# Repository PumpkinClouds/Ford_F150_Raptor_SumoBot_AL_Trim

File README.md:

# Ford_F150_Raptor_SumoBot_AL_Trim
Sumo Bot Designed by Minh Nguyen, David Hong, Nathan Wignall, and Ana Wise

This Repository contains the code and pcb design for the sumo bot.

The "Ford F150" is a unique 4 wheeled sumo bot

PCB Design Software: KiCad

Microcontroller used: STM32F303CCT6 ([datasheet]([url](https://www.st.com/content/ccc/resource/technical/document/datasheet/f2/1f/e1/41/ef/59/4d/50/DM00058181.pdf/files/DM00058181.pdf/jcr:content/translations/en.DM00058181.pdf)))

Microcontroller Programming Framework: 

3 IR Distance Sensors: Adafruit GP2Y0A21YK0F [Link]([url](https://www.adafruit.com/product/164)) 

4 JSumo ML1 Line Sensors: JSumo JS16249 [Link]([url](https://www.jsumo.com/micro-line-sensor-ml1))

Bot code and pcb for sumo bot competition. (Asgore's fault)

## Contributing to the Project

### Software Dependencies
- [ ] KiCAD
- [ ] A text editor
- [ ] (Optional) Nix + Flakes + Direnv, automatically sets up a development enviornment to work on the project with

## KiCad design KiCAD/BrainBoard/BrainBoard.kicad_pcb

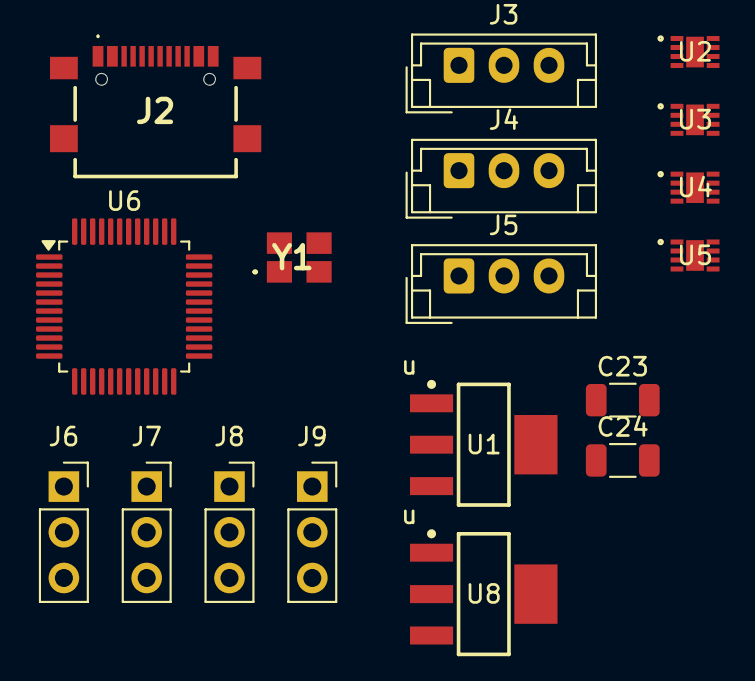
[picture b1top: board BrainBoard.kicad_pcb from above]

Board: 2 copper layers, 18 parts (0 on the bottom side), 25 nets, no tracks yet.

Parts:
C23: 0.47uF; C_1206_3216Metric
C24: 22uF; C_1206_3216Metric
J2: USB4216-03-A; USB421603A
J3, J4, J5: Conn_01x03_Socket; JST_EH_B3B-EH-A_1x03_P2.50mm_Vertical
J6, J7, J8, J9: Conn_01x03_Socket; PinSocket_1x03_P2.54mm_Vertical
U1: TLV1117-33; DCY0004A_N
U2, U3, U4, U5: DRV8231DSGR; WSON8_DRV8231_TEX
U6: STM32F303CCTx; LQFP-48_7x7mm_P0.5mm
U8: LM2940IMPX-5.0/NOPB; DCY0004A_N
Y1: NX3225SA-32.000MHZ-STD-CSR-1; NX3225SA32000MHZSTDCSR1

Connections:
+3.3V: J6.2, J7.2, J8.2, J9.2, U1.2 (VO), U2.4 (VREF), U3.4 (VREF), U4.4 (VREF), U5.4 (VREF), U6.1 (VBAT), U6.24 (VDD), U6.36 (VDD), U6.48 (VDD)
+5V: J3.1, J4.1, J5.1
+BATT: C23.1, U1.3 (VI), U2.5 (VM), U3.5 (VM), U4.5 (VM), U5.5 (VM), U8.1 (IN)
/Distance Sensors/DIST_SENS_1: J3.3, U6.21 (PB10)
/Distance Sensors/DIST_SENS_2: J4.3, U6.25 (PB12)
/Distance Sensors/DIST_SENS_3: J5.3, U6.26 (PB13)
/Line Sensors/LINE_1: J6.1, U6.13 (PA3)
/Line Sensors/LINE_2: J7.1, U6.19 (PB1)
/Line Sensors/LINE_3: J8.1, U6.38 (PA15)
/Line Sensors/LINE_4: J9.1, U6.45 (PB8)
/Motor Drivers/IN1_A: U3.3 (IN1), U6.11 (PA1)
/Motor Drivers/IN1_B: U2.3 (IN1), U6.16 (PA6)
/Motor Drivers/IN1_C: U4.3 (IN1), U6.43 (PB7)
/Motor Drivers/IN1_D: U5.3 (IN1), U6.27 (PB14)
/Motor Drivers/IN2_A: U3.2 (IN2), U6.12 (PA2)
/Motor Drivers/IN2_B: U2.2 (IN2), U6.17 (PA7)
/Motor Drivers/IN2_C: U4.2 (IN2), U6.42 (PB6)
/Motor Drivers/IN2_D: U5.2 (IN2), U6.28 (PB15)
/STM32F303CCT6 Microcontroller/HSE_IN: U6.5 (PF0), Y1.1 (XTAL_1)
/STM32F303CCT6 Microcontroller/HSE_OUT: U6.6 (PF1), Y1.3 (XTAL_2)
/STM32F303CCT6 Microcontroller/USB_D+: J2.A6 (DP1), J2.B6 (DP2), U6.33 (PA12)
/STM32F303CCT6 Microcontroller/USB_D-: J2.A7 (DN1), J2.B7 (DN2), U6.32 (PA11)
/STM32F303CCT6 Microcontroller/USB_VBUS: J2.A4 (VBUS_1), J2.B4 (VBUS_2)
/Voltage Regulator/5V: C24.1, U8.3 (OUT)
GND: C23.2, C24.2, J2.A1 (GND_1), J2.B1 (GND_2), J2.G1 (GND_3), J2.G2 (GND_4), J2.G3 (GND_5), J2.G4 (GND_6), J3.2, J4.2, J5.2, J6.3, J7.3, J8.3, J9.3, U1.1 (GND), U6.8 (VSSA), U6.23 (VSS), U6.35 (VSS), U6.47 (VSS), Y1.2 (GND_1), Y1.4 (GND_2)

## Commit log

2025-09-29 kicad files
2025-09-29 refactor: adding some dev files and reorganizing file structure
2025-09-29 docs: minimal update to README for contributions
2025-09-29 Update flakes with support for markdown and git utils
2025-09-30 add folders for footprints, symbols, and 3d-models
2025-09-30 [feat] add voltage regulator
2025-09-30 [bug] make ERC happy
2025-09-30 [docs] update page settings
2025-09-30 initial PIO project creation
2025-09-30 [fix] replace linear regulator
2025-09-30 [feat] add example motor driver
2025-10-02 [feature] Finalize DRV8231DSGR motor drivers
2025-10-06 feat: Processor add
2025-10-06 fix: Make DRC happy
2025-10-07 refactor(Software): change the PIO framework to `libopencm3`
2025-10-07 chore(Software): update .gitignore to ignore `.cache/` and `.platformio/`
2025-10-07 feat(Software): add additional project files (VSCode and .clang-format)
2025-10-07 feat(KiCad): Add a .gitignore for KiCad project
2025-10-13 feat: add second battery
2025-10-18 Added and finalized GPIO and PWM pinouts
2025-10-18 feat: added hierarchy pins to global sheet
2025-10-20 feat: Connect microcontroller pwm signals into motor drivers
2025-10-20 feat: battery input
2025-10-20 fix: correct nominal voltage
2025-10-24 refactor(Software): change framework from libopencm3 to stm32_hal
2025-10-24 feat(Software): Additional pin setup
2025-10-28 feat: added hiearchal power pins to microcontroller to avoid having global labels in hiearchal sheets
2025-10-28 feat: added micro-jst connector pins for distance sensors
2025-11-03 feat: Line sensor thing push
2025-11-04 Enhance README with project details and references
    Added project description, hardware details, and links.
2025-11-04 Enhance README with project details and links
    Updated README with additional details about the project.
2025-11-04 feat: add +5V line
2025-11-04 Assigned most general footprints
